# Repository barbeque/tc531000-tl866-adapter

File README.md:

# TC531000 to 27c010 adapter
This adapter board allows you to dump Toshiba TC531000 28-pin "mostly JEDEC" 1Mbit mask ROMs with a TL866 EPROM programmer by adapting the pinout to the more common 32-pin JEDEC 27c010 pinout.

It has been confirmed working for:

 - Hitachi HN62301

It has not yet been confirmed working for:

 - NEC µPD23c1000
 - TI TMS47c1024
 - Toshiba TC531000

**Status**: Partially tested.

## Bill of Materials

 - ZIF socket 28 pin (wide) or 28-pin DIP socket
 - Male pin headers
 - Jumper (optional)

## How to assemble
 1. Solder pin headers to the "27C010" portion of the board. The easiest way to keep these straight is to use a solderless breadboard.
 2. Solder pin headers to the jumper sections of the board. Connect a jumper across the "CE."
 3. Solder the 28-pin ZIF or DIP socket into the position for "TC531000."

## How to use
Install the ROM into the socket on the adapter. Install the adapter into the TL866. Pay very close attention to the orientation of the adapter and the ROM!

You can now dump ROMs using minipro:

```bash
minipro -p 27C010@DIP32 -r rom.bin -y
```

You will get a warning about incorrect chip ID; mask ROMs do not seem to obey this part of the standard. The `-y` is to ignore it.

I recommend doing multiple dumps and comparing them, to make sure there are no spotty connections.

## Credits
It was originally developed as part of a [Leaded Solder](https://www.leadedsolder.com) hardware project.

The ZIF socket footprint comes from the hard work of ayanosuke in the [kicad_zif-socket project](https://github.com/ayanosuke/kicad_zif-socket)

<br />This work is licensed under a <a rel="license" href="http://creativecommons.org/licenses/by-sa/4.0/">Creative Commons Attribution-ShareAlike 4.0 International License</a>.

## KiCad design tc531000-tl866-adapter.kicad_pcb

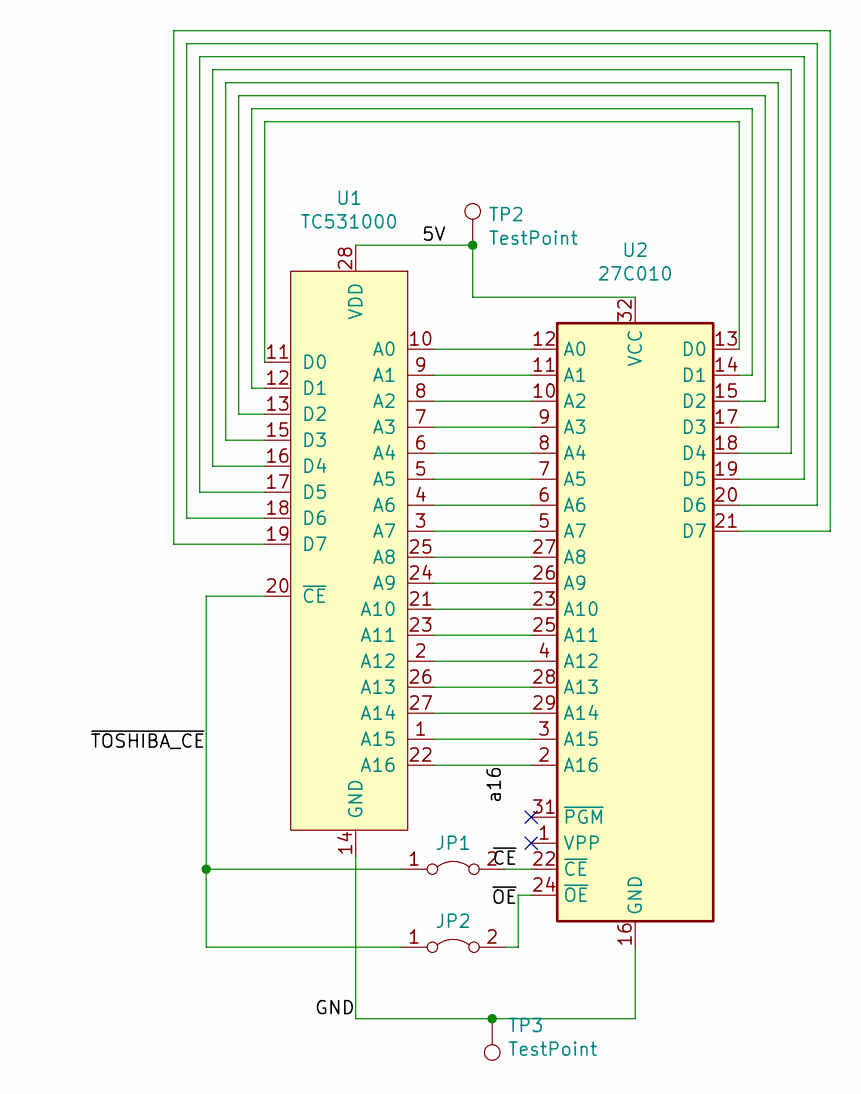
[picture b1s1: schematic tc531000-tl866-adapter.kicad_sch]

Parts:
JP1, JP2: Jumper_2_Bridged; PinHeader_1x02_P2.54mm_Vertical
TP2, TP3: TestPoint; TestPoint_Plated_Hole_D3.0mm
U1: TC531000; DIP-28_W15.24mm_Socket_LongPads
U2: 27C010; DIP-32_W15.24mm_Socket_LongPads

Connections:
/5V: TP2.1, U1.28 (VDD), U2.32 (VCC)
/GND: TP3.1, U1.14 (GND), U2.16 (GND)
/a16: U1.22 (A16), U2.2 (A16)
/~CE: JP1.2 (B), U2.22 (~CE)
/~OE: JP2.2 (B), U2.24 (~OE)
/~TOSHIBA_CE: JP1.1 (A), JP2.1 (A), U1.20 (~CE)
unnamed: U1.10 (A0), U2.12 (A0)
unnamed: U1.9 (A1), U2.11 (A1)
unnamed: U1.8 (A2), U2.10 (A2)
unnamed: U1.7 (A3), U2.9 (A3)
unnamed: U1.6 (A4), U2.8 (A4)
unnamed: U1.5 (A5), U2.7 (A5)
unnamed: U1.4 (A6), U2.6 (A6)
unnamed: U1.3 (A7), U2.5 (A7)
unnamed: U1.25 (A8), U2.27 (A8)
unnamed: U1.24 (A9), U2.26 (A9)
unnamed: U1.21 (A10), U2.23 (A10)
unnamed: U1.23 (A11), U2.25 (A11)
unnamed: U1.2 (A12), U2.4 (A12)
unnamed: U1.26 (A13), U2.28 (A13)
unnamed: U1.27 (A14), U2.29 (A14)
unnamed: U1.1 (A15), U2.3 (A15)
unnamed: U1.11 (D0), U2.13 (D0)
unnamed: U1.12 (D1), U2.14 (D1)
unnamed: U1.13 (D2), U2.15 (D2)
unnamed: U1.15 (D3), U2.17 (D3)
unnamed: U1.16 (D4), U2.18 (D4)
unnamed: U1.17 (D5), U2.19 (D5)
unnamed: U1.18 (D6), U2.20 (D6)
unnamed: U1.19 (D7), U2.21 (D7)

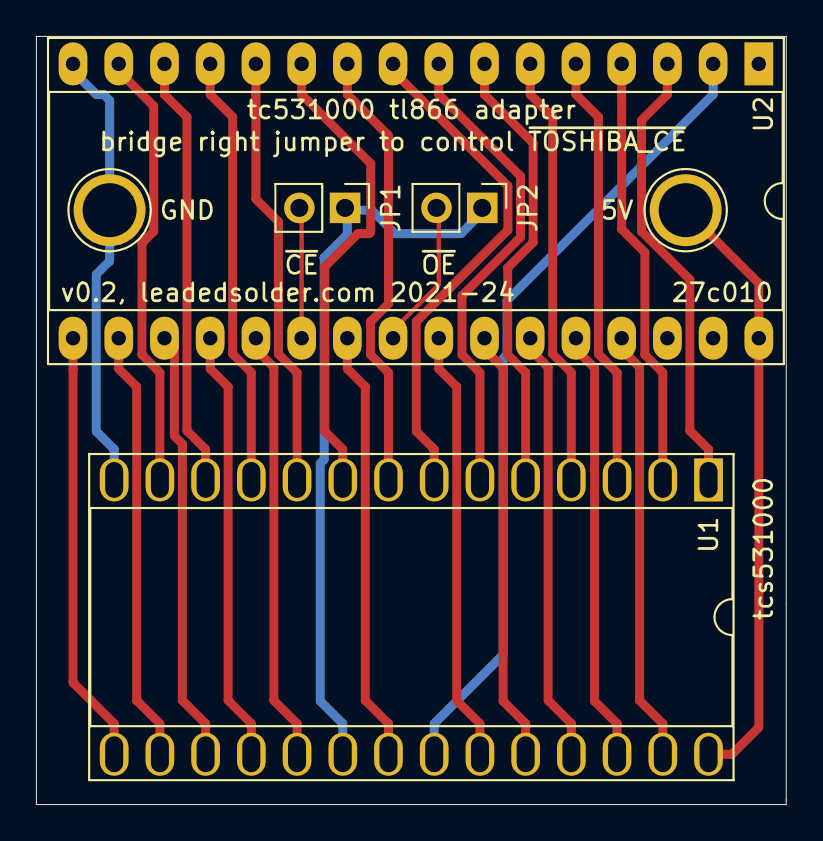
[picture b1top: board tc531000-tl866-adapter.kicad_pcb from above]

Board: 2 copper layers, 41.7 x 42.7 mm, 6 parts (0 on the bottom side), 30 nets.

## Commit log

2021-06-11 Initial version, way too big
2021-06-11 Mini version but overhang is on the wrong side
2021-06-11 V0.1 sent to osh
2021-06-11 Attribution for ZIF-socket
2021-10-04 Use a standard 28 pin DIP socket with some extra space around it. Wait for the ZIF to see if it fits
2024-02-07 Fix file for KiCad 7
2024-02-07 Hog out the holes so a ZIF socket fits better
2024-02-07 Plot v2
2024-02-07 Update status
2024-09-21 Found more ROMs that may interchange
2024-09-22 Instructions: I'll need them later
